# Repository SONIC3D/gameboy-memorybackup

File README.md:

# Gameboy MemoryBackup Cartridge
## Introduction
This is a gameboy game cartridge save memory backup device. By using this cart, you can transfer the save content from the gameboy cartridge SRAM to the flash memory. So that the data can be preserved without any cell battery.

And additionally, full MBC1 feature has been implemented. So it will support MBC1 games with ROM size no more than 512KB. MBC1 SRAM feature is also supported.

**Please note that the ROM content need to be programmed externally. It's not be able to load ROM content from the plugged-in cartridge in current version.**

## Updates:
* v1.0 (2023.Mar.15)
    * Implemented the basic routing.
* v1.1 (2023.Mar.17)
    * Redesigned the PCB for installing within original GameBoy cartridge shell. because producing 2.0mm PCB will cause unnecessary cost in JLCPCB.
* v1.2 (2023.Mar.17)
    * Captures the /Reset signal to latch the switch button state on power-on.(The original MemoryBackup cartridge has no such feature.)
* v1.3 (2023.Mar.26)
    * Most features of the cartridge hardware are finished. Implemented full MemoryBackup cartridge feature. And additionally, implemented MBC1 feature as addon(With known issue and minor difference).
* v1.4 (WIP)
    * Fixed the known issue in v1.3 and revise the design to make the MBC1 feature completely same as the original(Except the ROM size is limited to not over 512KB/4Mbit).
    * This is the first version I make the order for real PCB production.

## Requirements(v1.4):
* Basic soldering skill. Most components are in Through-Hole type.
* ATMEL JTAG ISP programmer for ATF15xx series.
    * Model number is ATDH1150USB. Digi-Key link: [Here](https://www.digikey.com/en/products/detail/microchip-technology/ATDH1150USB/2050869)
* ATMEL WinCUPL(If you need to modify the PLD source code):
    * [Download Page](https://www.microchip.com/en-us/products/fpgas-and-plds/spld-cplds/pld-design-resources). Please note you need to enter the S/N provided by ATMEL on this page during the installation .
    * [Documentations](https://www.microchip.com/en-us/development-tool/WinCUPL)
* ROM Programmer that support your main program ROM model.
    * For example, if you decide to use a SST 28SF040 or AT29C040 as the program ROM, you can consider [Xeltek Superpro 610p](https://www.xeltek-cn.com/en/universal-programmers/economy-universal-programmer-superpro-610p.html), check the device list to make sure your ROM is supported.
* Components:
    * Mainboard
        * PLCC-44 IC socket x1
        * PLCC-32 IC socket x2
        * DIP-32 IC socket x1
        * DIP-32 IC socket x1
        * CR1616 battery socket x1
        * SPDT Switch(90deg angled) x1
        * 2*16 PinSocket x1
        * 2*5 PinSocket x1(This is for ISP program the ATF15xx CPLD, if you have JTAG cable extender with a fixture, this PinSocket is not needed.)
        * Capacitor 0.1uF x6
        * Resistor 10K x3
        * Resistor 1K x3
        * ATF1502 PLCC44 x1(ATF1504 PLCC44 is also compatible, source code need to be modified)
        * SST 28SF040 PLCC32 Programmable ROM x1 (512KB Storage ROM)
        * 16KB-512KB PLCC32 Programmable ROM x1 (Main Program ROM. SST 28SF040 is also an acceptable model)
        * TC551001 DIP32 Static RAM x1 (Or other pin compatible 128KB/1Mbit Static RAM)
        * BA6162F battery supervisor chip x1
    * Subboard
        * NDSL GBA cartridge slot.(Search and grab one on aliexpress.)
        * 2*16 PinHeader x1

## ROM data for the main program
* I'm still creating my own program to implement the backup feature. But as this cartridge support the original Karat MemoryBackup, which is also known as "Mega Memory" or "Mega Memory Card" in other regions. You can also use the dumped ROM from these products. More Info:
    * [TCRF.NET](https://tcrf.net/Mega_Memory_Card_(Game_Boy))
    * [Manual(Archive.org)](https://archive.org/details/mega-memory-card-gameboy-manual-and-cart-hi-res-ozidual)
    * [ROM(Archive.org), filename "Mega Memory (World) (Unl).7z"](https://archive.org/details/nointro.gb)

## Tech detail on the Mapper Logic implemented in this cartridge(v1.4)
* (WIP)

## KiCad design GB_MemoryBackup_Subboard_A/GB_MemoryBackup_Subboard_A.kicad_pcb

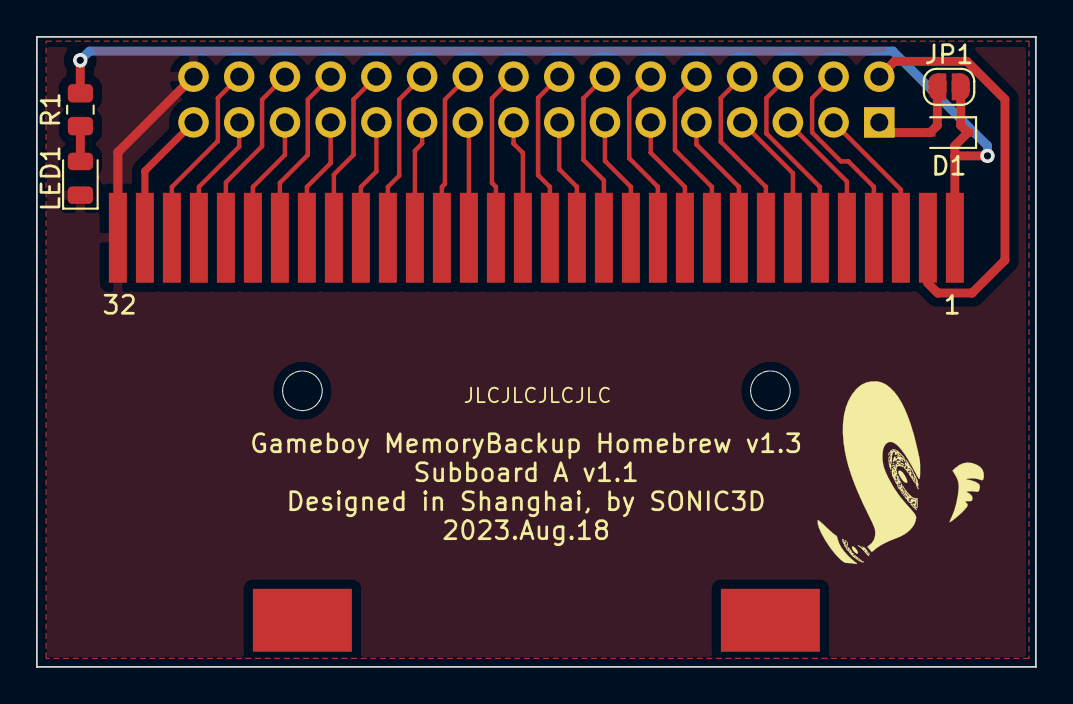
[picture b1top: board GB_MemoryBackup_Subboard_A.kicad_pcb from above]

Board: 2 copper layers, 55.5 x 35.0 mm, 6 parts (1 on the bottom side), 34 nets.

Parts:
D1: 1N4148WS; D_SOD-323
J1: Conn_02x16_Odd_Even; PinHeader_2x16_P2.54mm_Vertical
J2: GB_Cart_Slot-1Row-32Pins; GB_GBA_Cartridge_Slot
JP1: SJ_SkipDiode; SolderJumper-2_P1.3mm_Open_RoundedPad1.0x1.5mm
LED1: PowerLED_Red; D_0805_2012Metric
R1: 10K; R_0805_2012Metric

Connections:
+5V: D1.2, J1.1, JP1.1
/AA0: J1.6, J2.6
/AA1: J1.7, J2.7
/AA2: J1.8, J2.8
/AA3: J1.9, J2.9
/AA4: J1.10, J2.10
/AA5: J1.11, J2.11
/AA6: J1.12, J2.12
/AA7: J1.13, J2.13
/AA8: J1.14, J2.14
/AA9: J1.15, J2.15
/AA10: J1.16, J2.16
/AA11: J1.17, J2.17
/AA12: J1.18, J2.18
/AA13: J1.19, J2.19
/AA14: J1.20, J2.20
/AA15_T: J1.21, J2.21
/AAudioIn: J1.31, J2.31
/ACLK: J1.2, J2.2
/AD0: J1.22, J2.22
/AD1: J1.23, J2.23
/AD2: J1.24, J2.24
/AD3: J1.25, J2.25
/AD4: J1.26, J2.26
/AD5: J1.27, J2.27
/AD6: J1.28, J2.28
/AD7: J1.29, J2.29
/CartSlot_5V_Input: D1.1, J2.1, JP1.2, R1.2
/PwrLED_5V_Input: LED1.2, R1.1
/~ARD_T: J1.4, J2.4
/~ARST: J1.30, J2.30
/~ASRAM_CS: J1.5, J2.5
/~AWR_T: J1.3, J2.3
GND: J1.32, J2.32, LED1.1

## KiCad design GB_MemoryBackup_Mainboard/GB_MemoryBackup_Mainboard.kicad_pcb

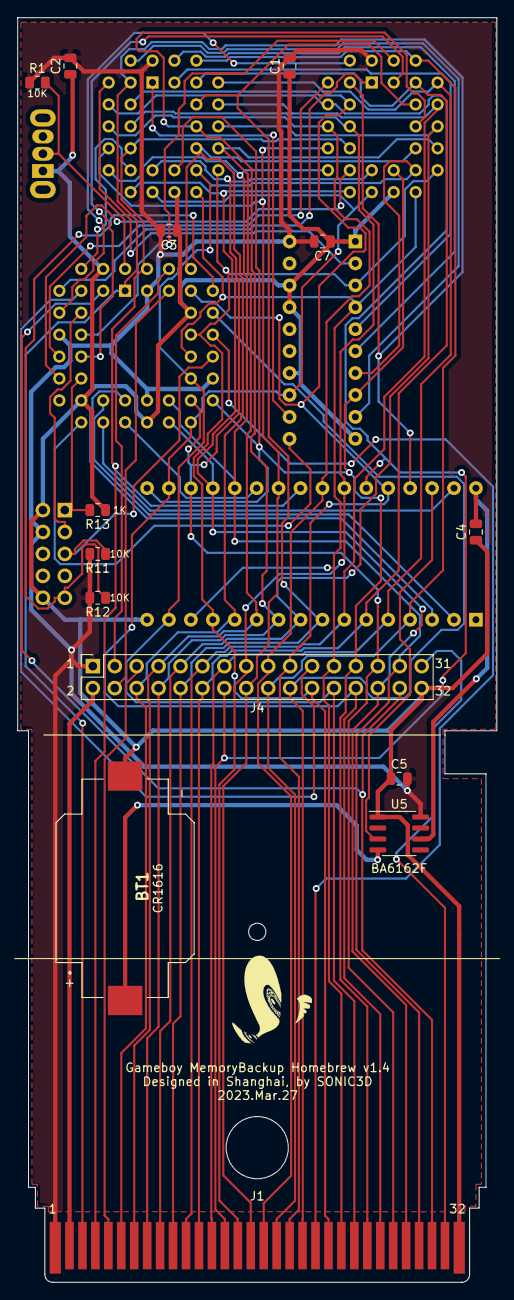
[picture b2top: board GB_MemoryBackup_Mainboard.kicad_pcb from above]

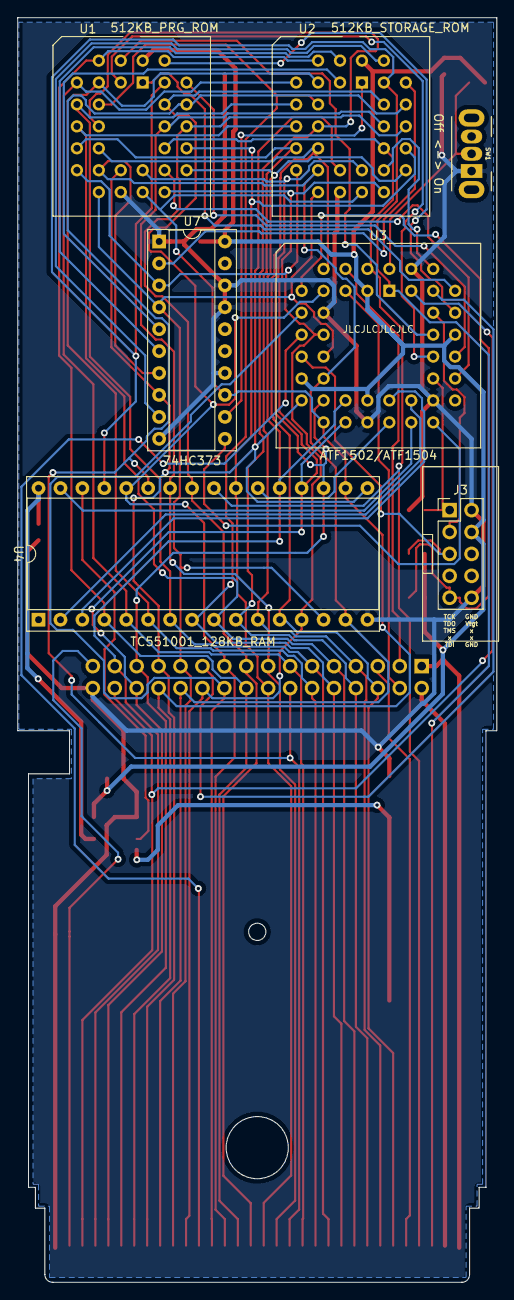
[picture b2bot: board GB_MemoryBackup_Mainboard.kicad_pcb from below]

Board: 2 copper layers, 55.5 x 146.5 mm, 21 parts (7 on the bottom side), 60 nets.

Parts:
BT1: 3V; BAT-SMD_CR1616
C1, C2, C3, C4, C5, C7: 0.1uF; C_0805_2012Metric
J1: GB_Cart_EdgeConn-1Row-32Pins; GB_Cart_1x32_P1.50mm_Edge_For_CartShell
J3: JTAG-A; PinHeader_2x05_P2.54mm_Vertical
J4: Conn_02x16_Odd_Even; PinSocket_2x16_P2.54mm_Vertical
R1, R11, R12: 10K; R_0805_2012Metric
R13: 1K; R_0805_2012Metric
SW1: SW_SPDT; SW-TH_SK12D07VG3
U1: AT29C010A-PLCC32; PLCC-32_THT-Socket
U2: 28SF040-120-4C-NH-PLCC32; PLCC-32_THT-Socket
U3: Generic-ATF15xx-PLCC44; PLCC-44_THT-Socket
U4: TC551001BPL_DIP32; DIP-32_W15.24mm_Socket
U5: BA6162F; SOIC-8_3.9x4.9mm_P1.27mm
U7: 74HC373; DIP-20_W7.62mm_Socket

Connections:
+5V: C1.2, C2.2, C3.2, C5.2, C7.2, J1.1, J3.4, J4.1, R1.1, R11.2, R12.2, U1.32, U2.32, U3.3, U3.15, U3.23, U3.35, U5.8, U7.20
/AA0: J1.6, J4.6, U1.12, U2.12, U3.6, U4.12
/AA1: J1.7, J4.7, U1.11, U2.11, U4.11
/AA2: J1.8, J4.8, U1.10, U2.10, U4.10
/AA3: J1.9, J4.9, U1.9, U2.9, U4.9
/AA4: J1.10, J4.10, U1.8, U2.8, U4.8
/AA5: J1.11, J4.11, U1.7, U2.7, U4.7
/AA6: J1.12, J4.12, U1.6, U2.6, U4.6
/AA7: J1.13, J4.13, U1.5, U2.5, U4.5
/AA8: J1.14, J4.14, U1.27, U2.27, U4.27
/AA9: J1.15, J4.15, U1.26, U2.26, U4.26
/AA10: J1.16, J4.16, U1.23, U2.23, U4.23
/AA11: J1.17, J4.17, U1.25, U2.25, U4.25
/AA12: J1.18, J4.18, U1.4, U2.4, U4.4
/AA13: J1.19, J4.19, U1.28, U2.28, U3.8, U4.28
/AA14: J1.20, J4.20, U3.9
/AA15: J1.21, U3.11
/AA15_T: J4.21, U3.41
/AAudioIn: J1.31, J4.31
/ACLK: J1.2, J4.2
/AD0: J1.22, J4.22, U1.13, U2.13, U3.12, U4.13, U7.3
/AD1: J1.23, J4.23, U1.14, U2.14, U3.14, U4.14, U7.4
/AD2: J1.24, J4.24, U1.15, U2.15, U3.16, U4.15, U7.7
/AD3: J1.25, J4.25, U1.17, U2.17, U3.17, U4.17, U7.8
/AD4: J1.26, J4.26, U1.18, U2.18, U3.18, U4.18, U7.13
/AD5: J1.27, J4.27, U1.19, U2.19, U3.19, U4.19
/AD6: J1.28, J4.28, U1.20, U2.20, U3.20, U4.20
/AD7: J1.29, J4.29, U1.21, U2.21, U3.21, U4.21
/F010_A14: U1.29, U3.33
/F010_A15: U1.3, U3.34
/F010_A16: U1.2, U3.36
/F010_A17: U1.30, U3.37
/F010_A18: U1.1, U3.39
/F040_A14: U2.29, U7.2
/F040_A15: U2.3, U7.5
/F040_A16: U2.2, U7.6
/F040_A17: U2.30, U7.9
/F040_A18: U2.1, U7.12
/HC373_040_LE: U3.28, U7.11
/RAM_A14: U3.25, U4.3
/RAM_A15: U3.26, U4.31
/RAM_A16: U3.27, U4.2
/RAM_CE2: U4.30, U5.3
/TCK: J3.1, R13.2, U3.32
/TDI: J3.9, R12.1, U3.7
/TDO: J3.3, U3.38
/TMS: J3.5, R11.1, U3.13
/~ARD: J1.4, U1.24, U2.24, U3.2, U4.24
/~ARD_T: J4.4, U3.5
/~ARST: J1.30, J4.30, U3.43
/~ASRAM_CS: J1.5, J4.5
/~AWR: J1.3, U1.31, U2.31, U3.1, U4.29
/~AWR_T: J4.3, U3.4
/~F_CE_010: U1.22, U3.31
/~F_CE_040: U2.22, U3.40
/~RAM_CE: U3.24, U4.22
/~SW_1: R1.2, SW1.2, U3.44
GND: BT1.2, C1.1, C2.1, C3.1, C4.1, C5.1, C7.1, J1.32, J3.2, J3.10, J4.32, R13.1, SW1.1, U1.16, U2.16, U3.10, U3.22, U3.30, U3.42, U4.16, U5.1, U7.1, U7.10, U7.14, U7.17, U7.18
unnamed: BT1.1, U5.4
VMEM: C4.2, U4.32, U5.6

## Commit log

2023-03-11 Added: Initial gitignore rules for KiCAD project.
2023-03-12 Added: Initial readme file.
2023-03-12 Added: External ATF15xx series CPLD symbols/footprints library repository.
2023-03-12 Added: External Gameboy cartridge components symbols/footprints library repository.
2023-03-12 Added: Common Flash ROM chip datasheet for using as main program ROM.
2023-03-12 Added: Common Flash ROM chip datasheet for using as main program ROM.(Alternative)
2023-03-12 Added: Common Flash ROM chip datasheet for using as save data storage target.
2023-03-12 Added: Common Flash ROM chip datasheet for using as save data storage target.(Later model of 28SF040)
2023-03-12 Added: CPLD datasheet.
2023-03-12 Added: CPLD datasheet.(ATF1504 PLCC-44, pin compatible to ATF1502)
2023-03-12 Modified: Datasheets directory renamed.
2023-03-12 Modified: git ignore rules moved.
2023-03-12 Added: KiCAD project settings for the GB MemoryBack mainboard design.
2023-03-13 Added: Schematic created, added edge connector, slot, CPLD and switch
2023-03-13 Added: CPLD JTAG port
2023-03-13 Added: Switch button 2 for additional control ability.
2023-03-13 Modified: Dependencies updated.
2023-03-13 Added: The main program ROM AT29C010/020/040 and the save backup storage ROM 28SF040/28SF040A
2023-03-13 Added: A lot of notes. CPLD equations and memory maps info.
2023-03-14 Modified: Added several footprint library for IC socket and JTAG port.
2023-03-14 Modified: Added footprint library for switch button and push button.
2023-03-14 Modified: Footprint id for most components.
2023-03-14 Modified: PLCC socket component id in JLCPCB.
2023-03-14 Added: Preliminary pcb components placement.
2023-03-14 Modified: Set PLCC-32 chips to use PLCC-32 socket SMD footprint.
2023-03-14 Modified: PCB updated with the updated footprints.
2023-03-14 Modified: PCB design updated
2023-03-14 Modified: Edge footprint has been changed.
2023-03-14 Modified: PCB design updated using Raw PCB setting.
2023-03-14 Modified: Changed PCB parameters for Net Class and PCB thickness.
2023-03-14 Modified: More keepout areas.
2023-03-14 Modified: Auto routed and manually revised.
2023-03-14 Added: My LogoGraphic footprints.
2023-03-14 Modified: Added copper filled zone. Modified: Added Logo and info text on PCB.
2023-03-14 Added: BOM file.
2023-03-14 Modified: Set the gerber output settings.
2023-03-14 Added: GerberOutput directory gitignore rules.
2023-03-14 Added: PCB v1.0 gerber files and pos files.
2023-03-14 Modified: POS file column title changed along to the JLCPCB standard.
2023-03-14 Modified: PCB redesigned for using with plastic cart shell.
2023-03-14 Modified: PCB thickness is changed to 0.8mm for installing with game cart shell.
2023-03-14 Modified: Moved PLCC-44 IC socket for the cartridge shell hole.
2023-03-14 Modified: Changed info text layer for auto routing.
2023-03-15 Modified: Added copper filled zone. Modified: PCB version updated to v1.1.
2023-03-15 Modified: PLCC-32 IC socket footprint updated from library.
2023-03-15 Added: Initial version of CPLD implementation.(Implementing a pass through cart.)
2023-03-15 Added: README file for CPLD source code directory.
2023-03-15 Modified: Full logic implemented using ATF1502AS PLCC-44.
2023-03-16 Modified: Assigned valid pinnode number for feedback node on ATF1502 PLCC-44.(By referencing the fitter document fit_app0.pdf, page 15)
2023-03-16 Modified: Equation logic on schematic sheet.
2023-03-16 Modified: v1.1 BOM
2023-03-16 Modified: v1.1 pcb gerber exported.
2023-03-16 Modified: v1.1 pos file.(JLCPCB format.)
2023-03-16 Modified: Commented push button and the pull-up resistor. Free the CPLD pin for connecting the /RST signal from cartridge slot.(For implement the latching of the switch button state value on power-on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
2023-03-16 Modified: Slightly modified the routing, syncing to the changes of the schematic.
2023-03-16 Added: v1.2 full logic implemented using ATF1502AS PLCC-44.
2023-03-17 Modified: v1.2 BOM
2023-03-17 Modified: v1.2 pcb gerber exported.
2023-03-17 Modified: v1.2 pos file.
2023-03-17 Modified: v1.2 pos file.(JLCPCB format.)
2023-03-17 Modified: v1.2 BOM copied to gerber output directory.
2023-03-18 Modified: Added 128KB SRAM and cell battery for implementing the full MBC1 save RAM support in future. Modified: Used 2 external 74HC373 for latching the high address line for main program ROM and st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
2023-03-18 Modified: Added footprint library cell battery holders.
2023-03-18 Modified: Footprints and JLCPCB component id.
2023-03-18 Modified: Use THT socket for PLCC-32 and PLCC-44 IC, for easier soldering by hand.
2023-03-18 Modified: PCB for v1.3 schematic.(Unrouted yet.)
2023-03-18 Added: Subboard A project.
2023-03-18 Added: Subboard A schematic.
2023-03-18 Added: Subboard A PCB.(Unrouted yet)
2023-03-18 Modified: Renamed component.
2023-03-18 Modified: PCB routed.
2023-03-18 Modified: Subboard v1.0 pcb gerber exported.
2023-03-18 Modified: Disabled GB Slot placement on PCB.
2023-03-18 Modified: PCB with Subboard-A slot.(Unrouted yet.)
2023-03-18 Modified: PCB components position modified for easier track routing.
2023-03-19 Modified: Audio line track width in net setting.
2023-03-19 Modified: PCB routed and manually revised. Modified: Added all info text labels on silk layers.
2023-03-19 Modified: v1.3 pcb gerber exported.
2023-03-19 Modified: v1.3 pos file.(JLCPCB format.)
2023-03-19 Modified: v1.3 BOM
2023-03-19 Modified: v1.3 BOM copied to gerber output directory.
2023-03-20 Modified: Swapped SW_1 and SW_2/ARST. For connecting /ARST to Global clk line, saving the product expression resource.
2023-03-20 Modified: Swapped SW_1 and SW_2/ARST on PCB project.
2023-03-20 Modified: v1.3 pcb gerber re-exported.
2023-03-20 Modified: Manually revised routing of several tracks.
2023-03-20 Modified: RAM need 8KB banking, so schematic is changed from banking through RAM_A16..A14 to RAM_A15..A13, and hold the A16 to always high.
2023-03-20 Modified: PCB modified based on the schematic.
2023-03-24 Revert "Modified: v1.3 pcb gerber re-exported."
    This reverts commit 0760941d7047ae5b69f201c7affc4bef0eac5c75.
2023-03-24 Revert "Modified: RAM need 8KB banking, so schematic is changed from banking through RAM_A16..A14 to RAM_A15..A13, and hold the A16 to always high."
    This reverts commit b47ffc313482a9c34a73032e10e4ca5aa5a3d764.
2023-03-24 Revert "Modified: PCB modified based on the schematic."
    This reverts commit fa85ecb86ebcad4c6abd318417a0d0b5febaa9af.
2023-03-25 Added: v1.3 full logic implemented using ATF1502AS PLCC-44.
2023-03-26 Added: Detailed v1.3 mapper logic documentation in Chinese.
2023-03-26 Modified: Removed preliminary redundant/incorrect notes in documentation.
2023-03-26 Added: Detailed v1.3 mapper logic documentation in English.
2023-03-26 Modified: v1.4 schematic. Hide the 74HC373 for PRG ROM banking. And integrate the banking logic to CPLD.
2023-03-26 Modified: PCB for v1.4 schematic.(Unrouted yet.)
2023-03-27 Modified: v1.4 PCB routed and manually revised.
2023-03-27 Modified: v1.4 pcb gerber exported.
2023-03-27 Modified: v1.4 BOM
2023-03-27 Modified: v1.4 BOM copied to gerber output directory.
2023-03-27 Modified: v1.4 pos file.(JLCPCB format.)
2023-03-27 Added: v1.4 full logic implemented using ATF1502AS PLCC-44.
2023-03-27 Added: CPLD code implemented the special logic of MBC1. Set actual ROM bank to $01 if user set the bank id to $00.
2023-03-27 Added: Update CPLD mapper logic documentation to v1.4.
2023-03-27 Modified: Info text on PCB silk and mask layers.
2023-03-27 Modified: v1.4 pcb gerber re-exported.
2023-03-27 Modified: Added JLCPCB batch string placement.
2023-03-27 Modified: v1.0 Subboard A pcb gerber re-exported.
2023-03-28 Modified: Updated the project README file.
2023-04-09 Added: Simplified memory backup feature only CPLD logic.(MBC1 feature are removed.)
2023-04-09 Fixed: It seems on falling edge of /WR signal, the address bus is ready, bu the data bus may not be ready all the times. It makes writing $80 to $2000 sometimes not switch the PrimaryMode_G0 to 0. So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
2023-04-09 Modified: Rename variable name and remove unused commented codes.
2023-04-09 Modified: Removed unused variables.
2023-04-09 Fixed: Output LatchEnable signal to 74HC373 later, to make it latch data bus on rising edge of /WR signal, same as the clk logic of the internal node PrimaryMode_G0.
2023-04-15 Fixed: Backup and restore failed to read nor write to the SRAM of the GameCart. The original ROM program requires the 0xA000-0xBFFF is read/write mapped to the GameCart even in mode that 28SF040 is m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
2023-04-15 Revised: Removed debugging pin exposed in last commit.
2023-04-16 Added: Mapper documentation for v1.4 [Simplified] mapper logic.
2023-04-22 Modified: Mapper documentation for v1.4 [Full] mapper logic. For I found the original code of MegaMemory/MemoryBackup requires additional mapping logic on accessing 0xA000-0xBFFF.
2023-04-23 Modified: Revised v1.4 [Simplified] mapper logic. The PrimaryMode flag now implemented with a not strictly correct but acceptable way on GameBoy. No macrocell register needed.
2023-08-18 Modified: SubBoard v1.1. Added diode, diode skipping solderjumper, and power indication led.
2023-08-18 Added: Gerber output for PCB v1.1.
